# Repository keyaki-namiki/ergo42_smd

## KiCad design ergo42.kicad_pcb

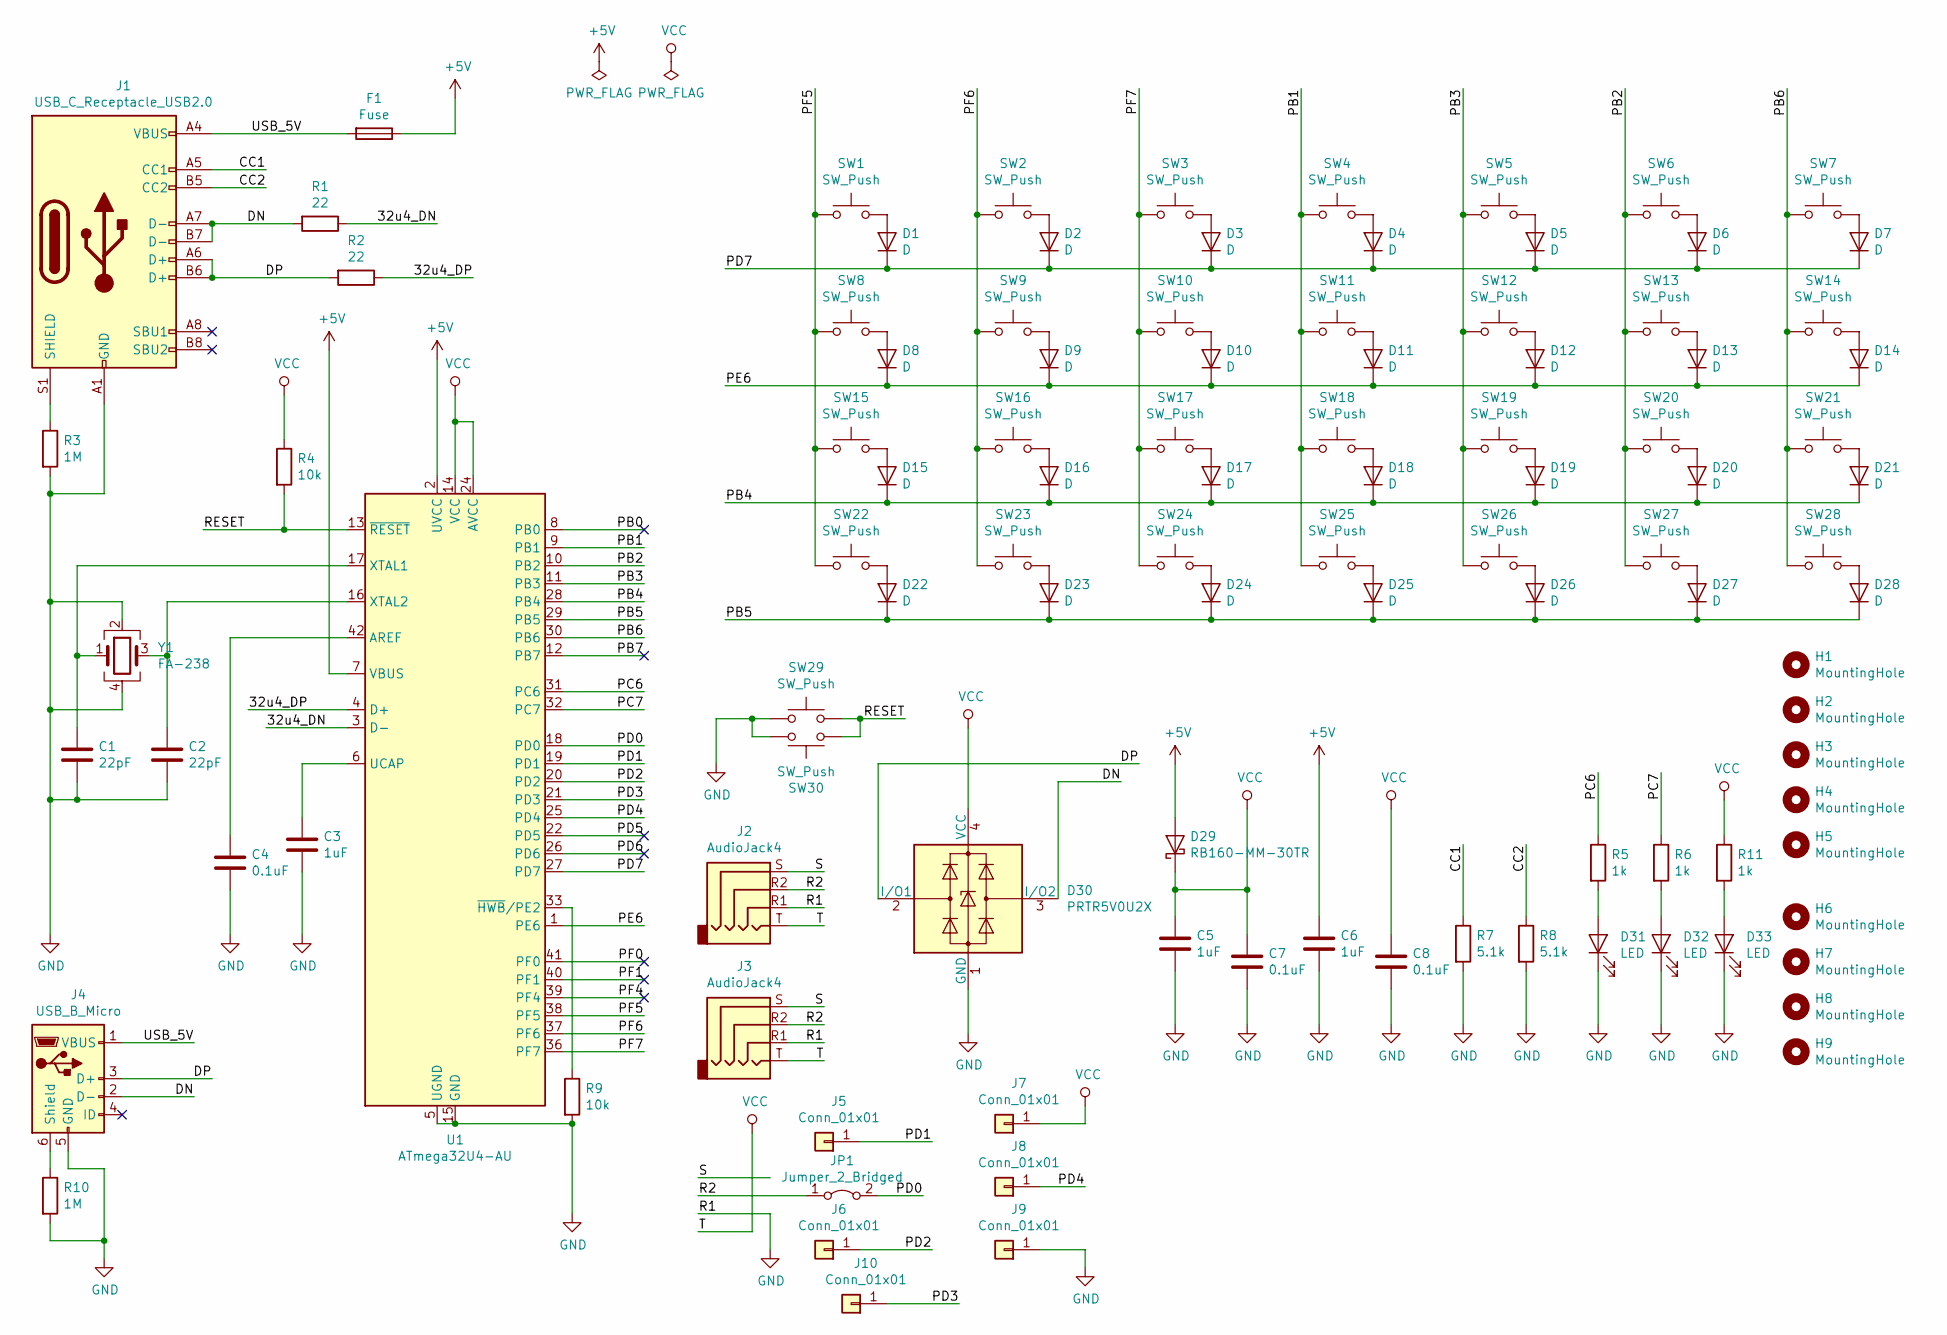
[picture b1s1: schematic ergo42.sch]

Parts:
C1, C2: 22pF; C_0603_1608Metric_Pad1.05x0.95mm_HandSolder
C3, C5, C6: 1uF; C_0603_1608Metric_Pad1.05x0.95mm_HandSolder
C4, C7, C8: 0.1uF; C_0603_1608Metric_Pad1.05x0.95mm_HandSolder
D1, D2, D3, D4, D5, D6, D7, D8, D9, D10, D11, D12, D13, D14, D15, D16, D17, D18, D19, D20, D21, D22, D23, D24, D25, D26, D27, D28: D; D_SOD-123
D29: RB160-MM-30TR; D_SOD-123F
D30: PRTR5V0U2X; SOT-143
D31, D32, D33: LED; LED_0805_2012Metric_Pad1.15x1.40mm_HandSolder
F1: Fuse; Fuse_1206_3216Metric_Pad1.42x1.75mm_HandSolder
H1, H2, H3, H4, H5: MountingHole; TestPoint_Plated_Hole_D5.0mm_noREFs
H6, H7, H8, H9: MountingHole; MountingHole_2.2mm_M2_Pad-noREFs
J1: USB_C_Receptacle_USB2.0; USB_C_Receptacle_GCT_USB4085-reAnchored
J2, J3: AudioJack4; 4pin_jack
J4: USB_B_Micro; USB_Micro-B_Molex-105017-0001
J5, J6, J7, J8, J9, J10: Conn_01x01; TestPoint_THTPad_1.0x1.0mm_Drill0.5mm
JP1: Jumper_2_Bridged; SolderJumper-2_P1.3mm_Bridged_Pad1.0x1.5mm
R1, R2: 22; R_0603_1608Metric_Pad1.05x0.95mm_HandSolder
R3, R10: 1M; R_0603_1608Metric_Pad1.05x0.95mm_HandSolder
R4, R9: 10k; R_0603_1608Metric_Pad1.05x0.95mm_HandSolder
R5, R6, R11: 1k; R_0603_1608Metric_Pad1.05x0.95mm_HandSolder
R7, R8: 5.1k; R_0603_1608Metric_Pad1.05x0.95mm_HandSolder
SW1, SW2, SW3, SW4, SW5, SW6, SW7, SW8, SW9, SW10, SW11, SW12, SW13, SW14, SW15, SW16, SW17, SW18, SW19, SW20, SW21, SW22, SW23, SW24, SW25, SW26, SW27, SW28: SW_Push; CherryMX_Hotswap
SW29, SW30: SW_Push; SW_SPST_TL3342
U1: ATmega32U4-AU; TQFP-44_10x10mm_P0.8mm
Y1: FA-238; Crystal_SMD_SeikoEpson_FA238-4Pin_3.2x2.5mm

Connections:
+5V: C6.1, D29.2 (A), F1.1, U1.2 (UVCC), U1.7 (VBUS)
/32u4_DN: R1.1, U1.3 (D-)
/32u4_DP: R2.1, U1.4 (D+)
/CC1: J1.A5 (CC1), R7.1
/CC2: J1.B5 (CC2), R8.1
/DN: D30.3 (I/O2), J1.A7 (D-), J1.B7 (D-), J4.2 (D-), R1.2
/DP: D30.2 (I/O1), J1.A6 (D+), J1.B6 (D+), J4.3 (D+), R2.2
/PB0: U1.8 (PB0)
/PB1: SW4.1, SW11.1, SW18.1, SW25.1, U1.9 (PB1)
/PB2: SW6.1, SW13.1, SW20.1, SW27.1, U1.10 (PB2)
/PB3: SW5.1, SW12.1, SW19.1, SW26.1, U1.11 (PB3)
/PB4: D15.1 (K), D16.1 (K), D17.1 (K), D18.1 (K), D19.1 (K), D20.1 (K), D21.1 (K), U1.28 (PB4)
/PB5: D22.1 (K), D23.1 (K), D24.1 (K), D25.1 (K), D26.1 (K), D27.1 (K), D28.1 (K), U1.29 (PB5)
/PB6: SW7.1, SW14.1, SW21.1, SW28.1, U1.30 (PB6)
/PB7: U1.12 (PB7)
/PC6: R5.1, U1.31 (PC6)
/PC7: R6.1, U1.32 (PC7)
/PD0: JP1.2 (B), U1.18 (PD0)
/PD1: J5.1, U1.19 (PD1)
/PD2: J6.1, U1.20 (PD2)
/PD3: J10.1, U1.21 (PD3)
/PD4: J8.1, U1.25 (PD4)
/PD5: U1.22 (PD5)
/PD6: U1.26 (PD6)
/PD7: D1.1 (K), D2.1 (K), D3.1 (K), D4.1 (K), D5.1 (K), D6.1 (K), D7.1 (K), U1.27 (PD7)
/PE6: D8.1 (K), D9.1 (K), D10.1 (K), D11.1 (K), D12.1 (K), D13.1 (K), D14.1 (K), U1.1 (PE6)
/PF0: U1.41 (PF0)
/PF1: U1.40 (PF1)
/PF4: U1.39 (PF4)
/PF5: SW1.1, SW8.1, SW15.1, SW22.1, U1.38 (PF5)
/PF6: SW2.1, SW9.1, SW16.1, SW23.1, U1.37 (PF6)
/PF7: SW3.1, SW10.1, SW17.1, SW24.1, U1.36 (PF7)
/R2: J2.R2, J3.R2, JP1.1 (A)
/RESET: R4.2, SW29.2, SW30.2, U1.13 (~RESET)
/S: J2.S, J3.S
/USB_5V: F1.2, J1.A4 (VBUS), J1.A9 (VBUS), J1.B4 (VBUS), J1.B9 (VBUS), J4.1 (VBUS)
GND: C1.2, C2.2, C3.2, C4.2, C5.2, C6.2, C7.2, C8.2, D30.1 (GND), D31.1 (K), D32.1 (K), D33.1 (K), J1.A1 (GND), J1.A12 (GND), J1.B1 (GND), J1.B12 (GND), J2.R1, J3.R1, J4.5 (GND), J9.1, R3.2, R7.2, R8.2, R9.2, R10.2, SW29.1, SW30.1, U1.5 (UGND), U1.15 (GND), U1.23 (GND), U1.35 (GND), U1.43 (GND), Y1.2, Y1.4
unnamed: C1.1, U1.17 (XTAL1), Y1.1
unnamed: C2.1, U1.16 (XTAL2), Y1.3
unnamed: C3.1, U1.6 (UCAP)
unnamed: C4.1, U1.42 (AREF)
unnamed: D1.2 (A), SW1.2
unnamed: D2.2 (A), SW2.2
unnamed: D3.2 (A), SW3.2
unnamed: D4.2 (A), SW4.2
unnamed: D5.2 (A), SW5.2
unnamed: D6.2 (A), SW6.2
unnamed: D7.2 (A), SW7.2
unnamed: D8.2 (A), SW8.2
unnamed: D9.2 (A), SW9.2
unnamed: D10.2 (A), SW10.2
unnamed: D11.2 (A), SW11.2
unnamed: D12.2 (A), SW12.2
unnamed: D13.2 (A), SW13.2
unnamed: D14.2 (A), SW14.2
unnamed: D15.2 (A), SW15.2
unnamed: D16.2 (A), SW16.2
unnamed: D17.2 (A), SW17.2
unnamed: D18.2 (A), SW18.2
unnamed: D19.2 (A), SW19.2
unnamed: D20.2 (A), SW20.2
unnamed: D21.2 (A), SW21.2
unnamed: D22.2 (A), SW22.2
unnamed: D23.2 (A), SW23.2
unnamed: D24.2 (A), SW24.2
unnamed: D25.2 (A), SW25.2
unnamed: D26.2 (A), SW26.2
unnamed: D27.2 (A), SW27.2
unnamed: D28.2 (A), SW28.2
unnamed: D31.2 (A), R5.2
unnamed: D32.2 (A), R6.2
unnamed: D33.2 (A), R11.2
unnamed: J1.S1 (SHIELD), R3.1
unnamed: J4.6 (Shield), R10.1
unnamed: R9.1, U1.33 (~HWB~/PE2)
VCC: C5.1, C7.1, C8.1, D29.1 (K), D30.4 (VCC), J2.T, J3.T, J7.1, R4.1, R11.1, U1.14 (VCC), U1.24 (AVCC), U1.34 (VCC), U1.44 (AVCC)

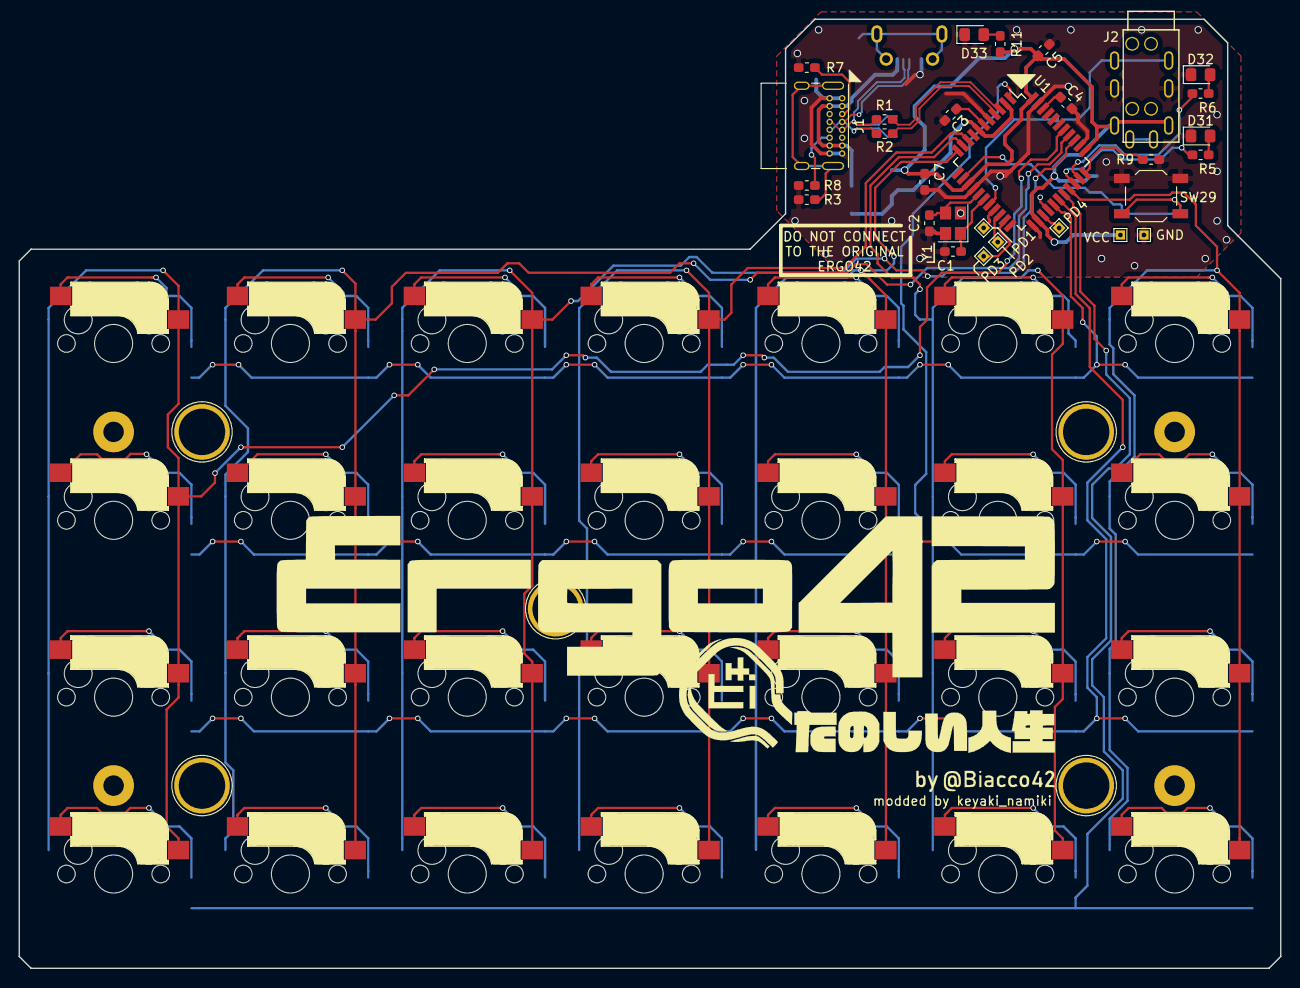
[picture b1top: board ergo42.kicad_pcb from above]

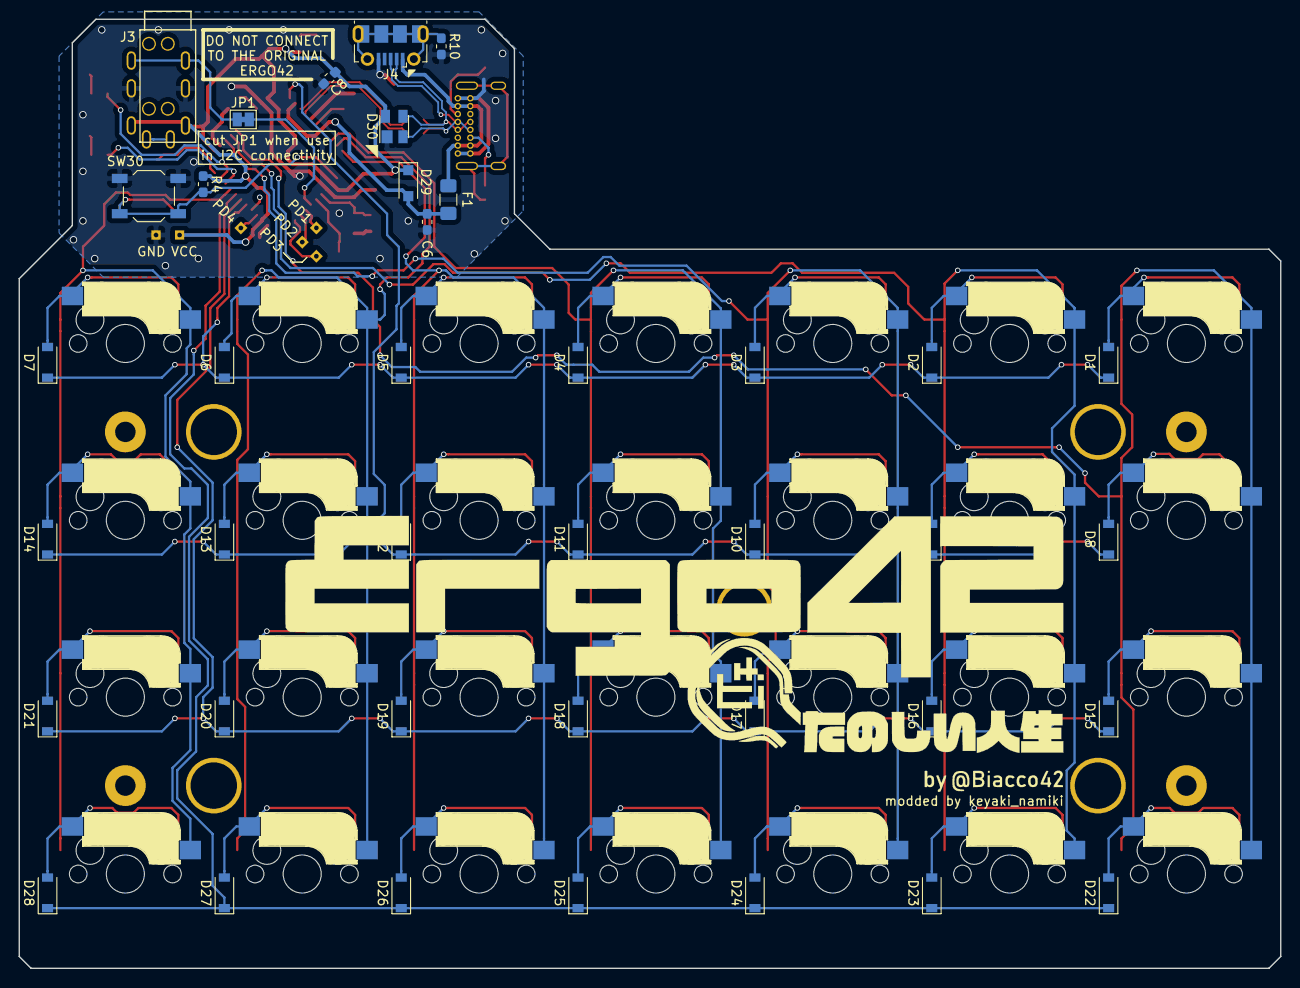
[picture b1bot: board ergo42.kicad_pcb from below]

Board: 2 copper layers, 135.9 x 102.2 mm, 105 parts (39 on the bottom side), 69 nets.

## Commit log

2020-01-30 add submodules
